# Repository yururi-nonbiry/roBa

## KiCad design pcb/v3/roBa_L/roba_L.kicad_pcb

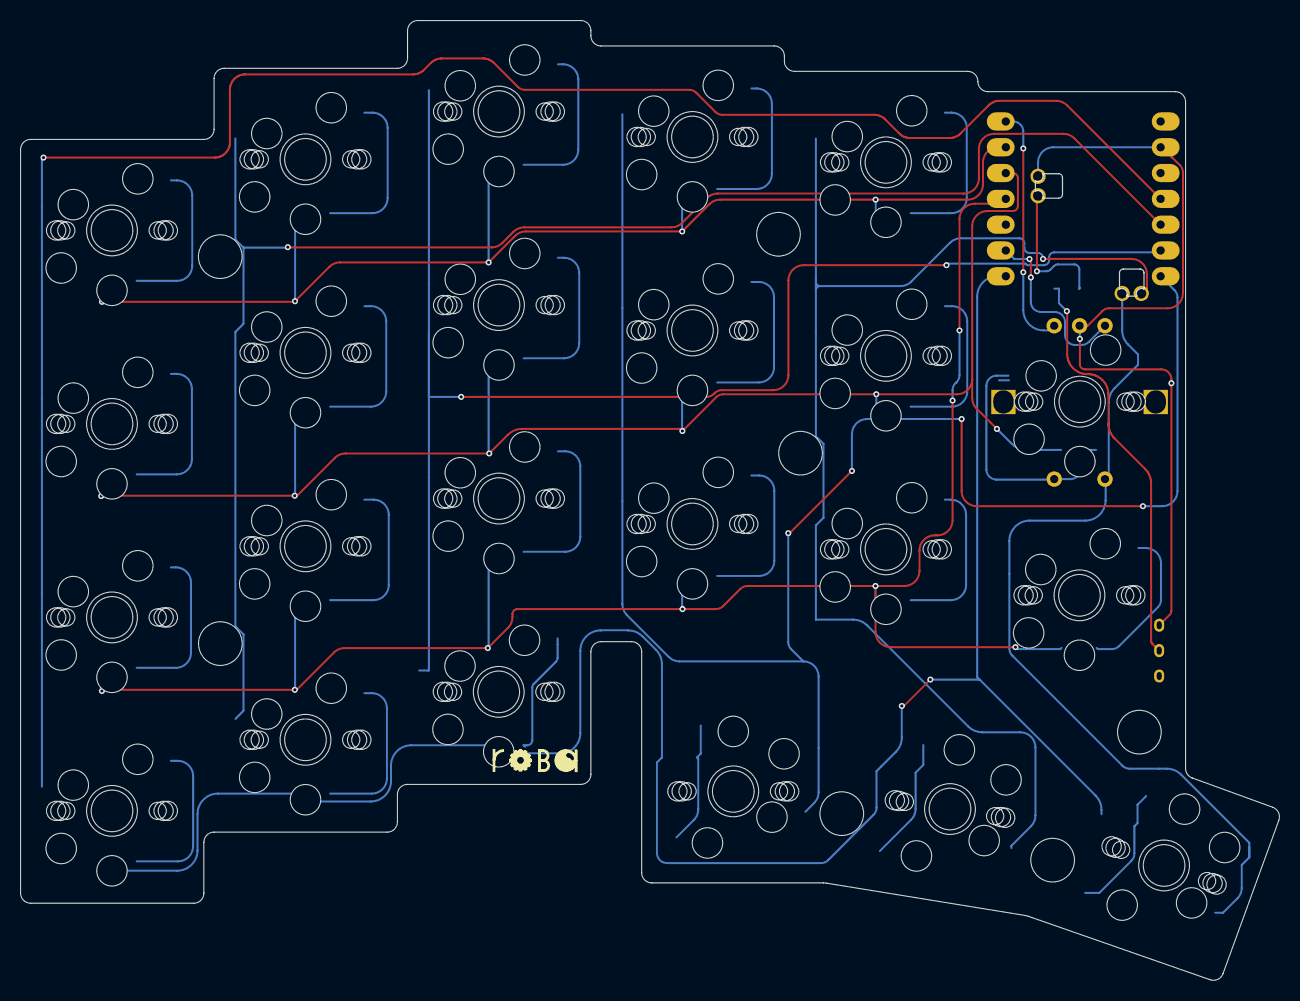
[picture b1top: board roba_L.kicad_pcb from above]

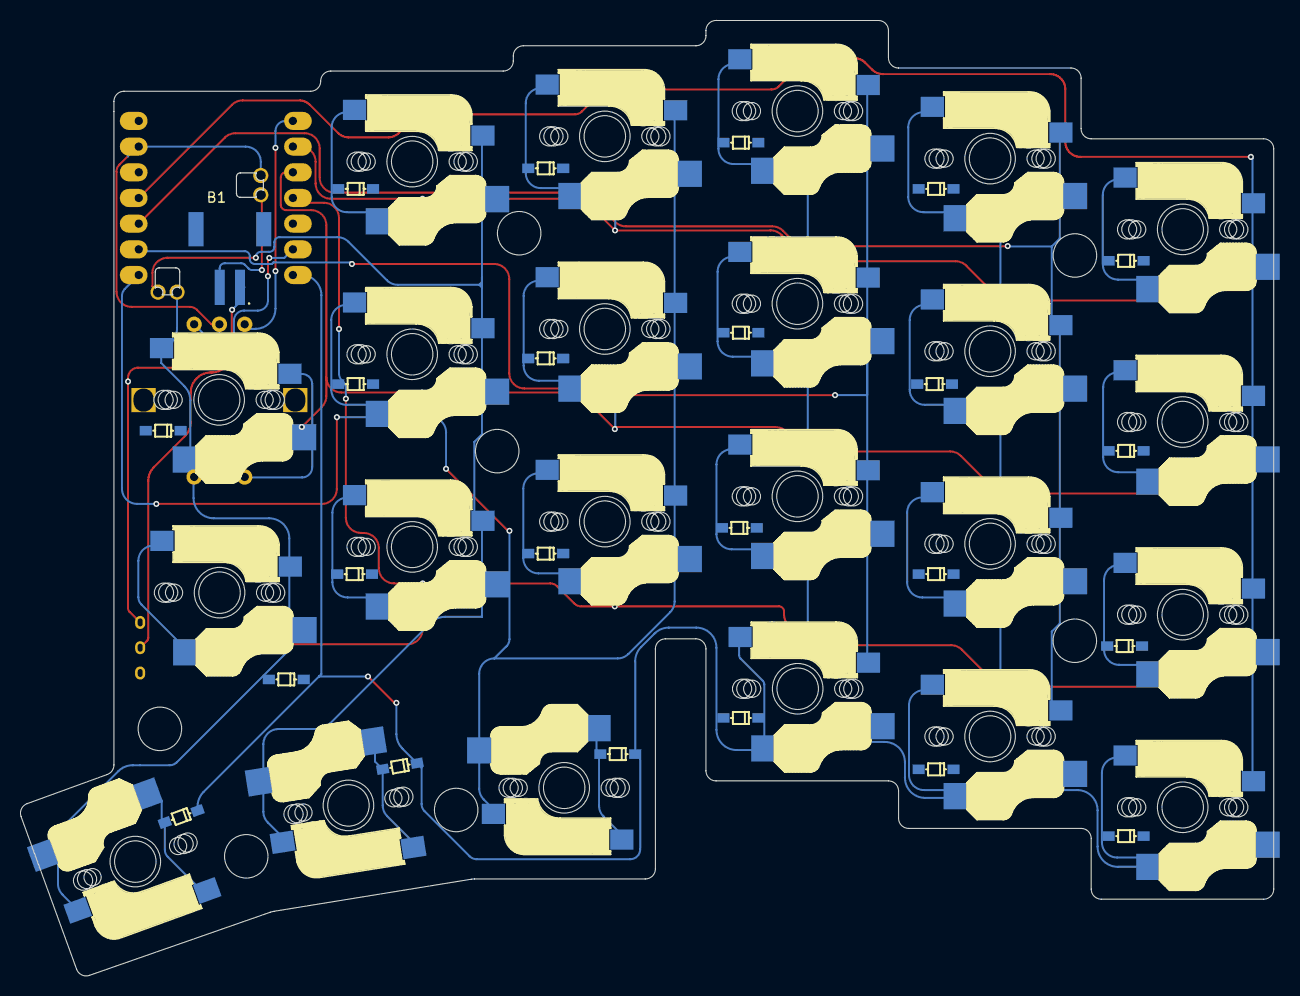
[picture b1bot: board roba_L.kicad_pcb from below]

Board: 2 copper layers, 123.9 x 94.5 mm, 57 parts (2 on the bottom side), 38 nets.

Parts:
B1: BATT; JST_S2B-PH-SM4-TB
D1, D2, D3, D4, D5, D6, D7, D8, D9, D10, D11, D12, D13, D14, D15, D16, D17, D18, D19, D20, D21, D22, D23: D; Diode_SMD
J1, J2, J3, J4, J5, J6, J7: Conn_01x01-Connector_Generic; MountingHole_4.3mm_M4
RTSW: RotaryEncoder_Switch; SW_MX_EC12
SW1, SW2, SW3, SW4, SW5, SW6, SW7, SW8, SW9, SW11, SW12, SW13, SW14, SW15, SW16, SW16#2, SW16#3, SW17, SW18, SW19, SW20, SW21, SW23: SW_PUSH; SW_MX_Choc
SW24: SW_SPDT; TGSW_MSK-12D19
U1: XIAO_nRF52840_wBAT_wNFC_1

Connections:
Bat: B1.1 (+), U1.20 (BATT+)
Col0: SW1.1, SW2.1, SW3.1, SW4.1, U1.11 (P1.15_D10_MOSI)
Col1: SW5.1, SW6.1, SW7.1, SW8.1, U1.10 (P1.14_D9_MISO)
Col2: SW9.1, SW11.1, SW12.1, SW16#3.1, U1.9 (P1.13_D8_SCK)
Col3: SW13.1, SW14.1, SW15.1, SW16#2.1, U1.8 (P1.12_D7_RX)
Col4: SW17.1, SW18.1, SW19.1, SW20.1, U1.16 (NFC2_0.10)
Col5: RTSW.2, SW16.1, SW21.1, SW23.1, U1.15 (NFC1_0.09)
GND: RTSW.C, SW24.3 (C), U1.13 (GND), U1.21 (BATT-)
unnamed: B1.2 (-), SW24.2 (B)
unnamed: D1.2 (A), SW1.2
unnamed: D2.2 (A), SW2.2
unnamed: D3.2 (A), SW3.2
unnamed: D4.2 (A), SW4.2
unnamed: D5.2 (A), SW5.2
unnamed: D6.2 (A), SW6.2
unnamed: D7.2 (A), SW7.2
unnamed: D8.2 (A), SW8.2
unnamed: D9.2 (A), SW9.2
unnamed: D10.2 (A), SW16#3.2
unnamed: D11.2 (A), SW11.2
unnamed: D12.2 (A), SW12.2
unnamed: D13.2 (A), SW13.2
unnamed: D14.2 (A), SW14.2
unnamed: D15.2 (A), SW15.2
unnamed: D16.2 (A), SW16#2.2
unnamed: D17.2 (A), SW17.2
unnamed: D18.2 (A), SW18.2
unnamed: D19.2 (A), SW19.2
unnamed: D20.2 (A), SW20.2
unnamed: D21.2 (A), RTSW.1, SW21.2
unnamed: D22.2 (A), SW16.2
unnamed: D23.2 (A), SW23.2
RE_A1: RTSW.A, U1.6 (P0.05_A5_D5_SCL)
RE_B: RTSW.B, U1.1 (P0.02_A0_D0)
Row0: D1.1 (K), D5.1 (K), D9.1 (K), D13.1 (K), D17.1 (K), U1.2 (P0.03_A1_D1)
Row1: D2.1 (K), D6.1 (K), D10.1 (K), D14.1 (K), D18.1 (K), D21.1 (K), U1.3 (P0.28_A2_D2)
Row2: D3.1 (K), D7.1 (K), D11.1 (K), D15.1 (K), D19.1 (K), D22.1 (K), U1.4 (P0.29_A3_D3)
Row3: D4.1 (K), D8.1 (K), D12.1 (K), D16.1 (K), D20.1 (K), D23.1 (K), U1.7 (P1.11_D6_TX)

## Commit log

2026-05-12 v3追加 Lロープロファイル追加
